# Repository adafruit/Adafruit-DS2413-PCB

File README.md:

## DS2413 1-Wire Two GPIO Controller Breakout PCB
<a href="http://www.adafruit.com/products/1551"><br/>
Click here to purchase one from the Adafruit shop</a>

You're too cool for I2C, and SPI has so many wires, 8-bit parallel... how can that be fashionable!? You are a 1-Wire kinda gal, and you want more 1-Wire breakouts in your life to complement all of your great engineering. Well rock on, because here you go, it's a 1-Wire controller with two open-drain GPIO.

You can put as many of the DS2413's as you want on a single I/O line, each one is uniquely addressable and shares the single I/O pin happily. The two controllable I/O lines (PIOA and PIOB) can be used as inputs or outputs. They are open-drain, so if you want to power an LED or something, you'll need a remote power supply (see Maxim's product page for more details)

PCB files for the Adafruit DS2413 1-Wire GPIO Breakout, The format is EagleCAD schematic and board layout
- http://www.adafruit.com/products/1551

### License

Adafruit invests time and resources providing this open source design, please support Adafruit and open-source hardware by purchasing products from [Adafruit](https://www.adafruit.com)!

All text above must be included in any redistribution

Designed by Limor Fried/Ladyada for Adafruit Industries.
Creative Commons Attribution/Share-Alike, all text above must be included in any redistribution. 
See license.txt for additional information.

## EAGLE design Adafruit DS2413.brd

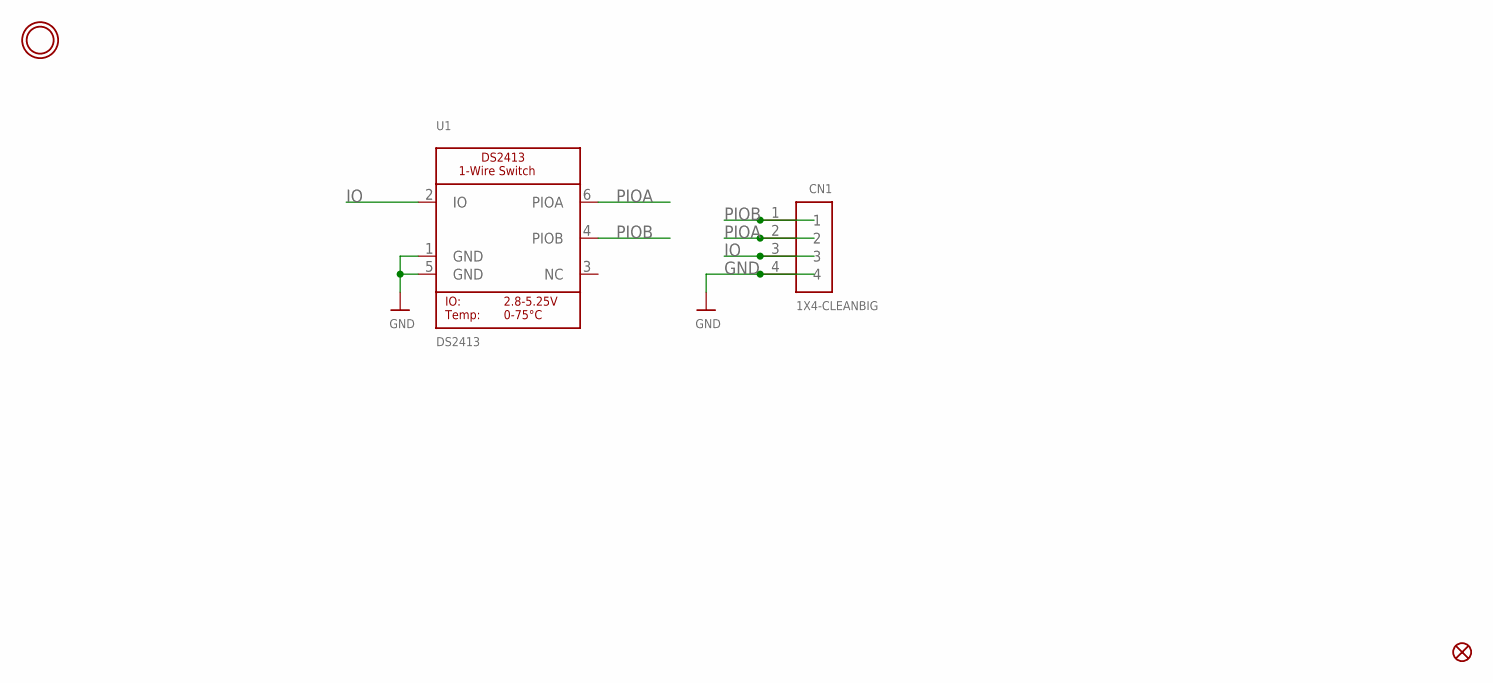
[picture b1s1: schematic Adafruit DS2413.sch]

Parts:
CN1: 1X4-CLEANBIG; 1X04-CLEANBIG
FID1: FIDUCIAL""; FIDUCIAL_1MM
U1: DS2413; DS2413_TSOC6L
U$4: MOUNTINGHOLE2.5; MOUNTINGHOLE_2.5_PLATED

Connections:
GND: CN1.4, U1.1 (GND), U1.5 (GND)
IO: CN1.3, U1.2 (IO)
PIOA: CN1.2, U1.6 (PIOA)
PIOB: CN1.1, U1.4 (PIOB)

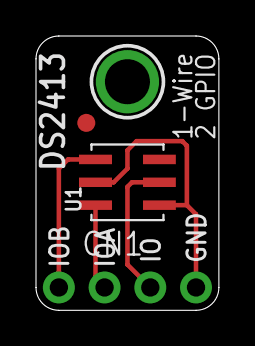
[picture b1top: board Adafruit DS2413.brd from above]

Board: 2 copper layers, 10.2 x 15.2 mm, 5 parts (1 on the bottom side), 4 nets.

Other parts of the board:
U$3: ADAFRUIT_3.5MM

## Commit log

2016-09-22 init

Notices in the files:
parts and their libraries:
microbuilder: This work is placed in the public domain, and may be freely used for commercial and non-commercial work with the following conditions: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
